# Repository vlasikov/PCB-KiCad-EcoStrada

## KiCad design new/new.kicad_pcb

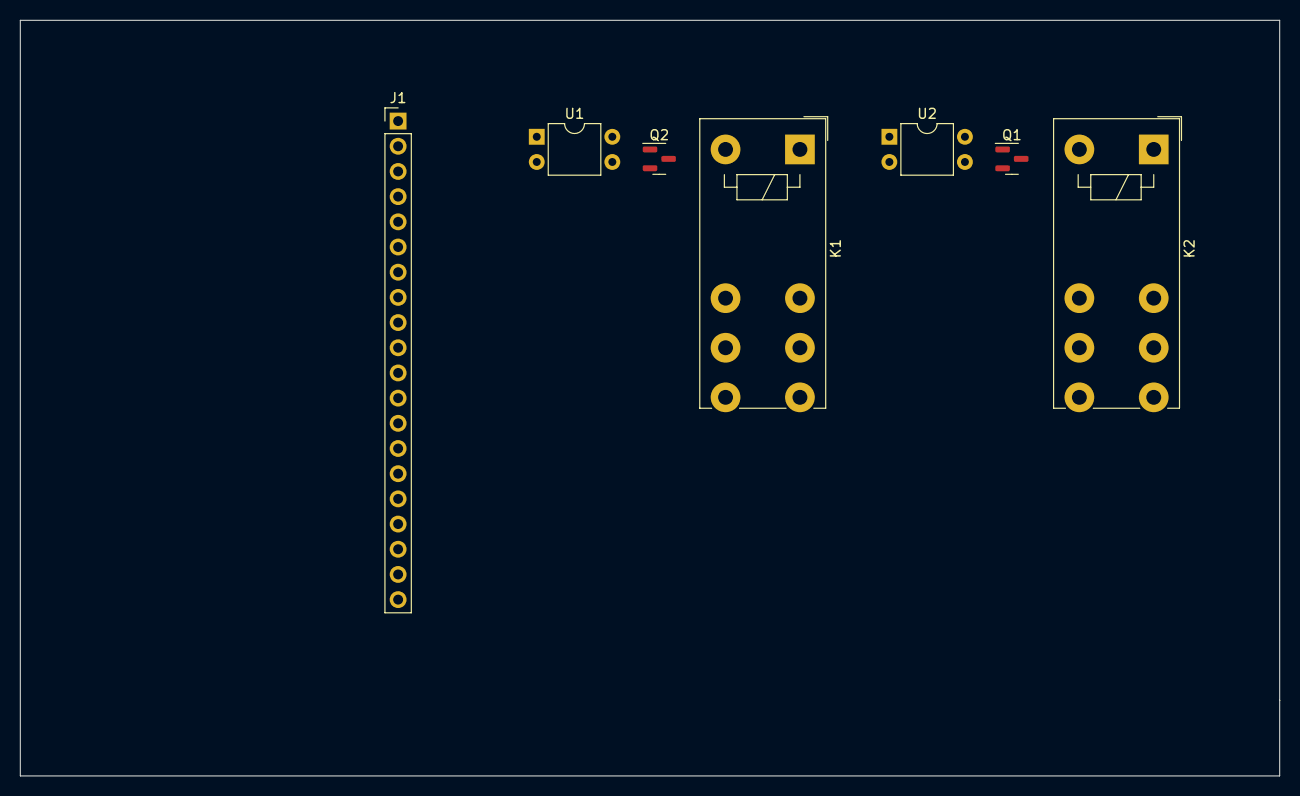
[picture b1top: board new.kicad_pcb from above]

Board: 2 copper layers, 127.0 x 76.2 mm, 7 parts (0 on the bottom side), 7 nets, no tracks yet.

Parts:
J1: Conn_01x20_Male; PinHeader_1x20_P2.54mm_Vertical
K1, K2: RSM822; Relay_DPDT_Finder_40.52
Q1, Q2: 2N7002; SOT-23
U1, U2: EL817; DIP-4_W7.62mm

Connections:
+5V: K1.A1, K2.A1
GND: Q1.2 (S), Q2.2 (S), U1.3, U2.3
GNDD: U1.2, U2.2
unnamed: K1.A2, Q2.3 (D)
unnamed: K2.A2, Q1.3 (D)
unnamed: Q1.1 (G), U2.4
unnamed: Q2.1 (G), U1.4
